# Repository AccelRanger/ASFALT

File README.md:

# ASFALT
**Accel Systems Line Following Robot**

A high-resolution line follower or edge follower calibrated for both usecases (TRD < for edge following, normal for line following) built on an Arduino Nano (ATmega328P), featuring a 16-sensor U-shaped IR array, custom KiCad PCBs, 3D-printed chassis parts, and a PID/proportional control algorithm with priority-based corner handling.

## License

This project is open source. Hardware designs, firmware, and mechanical files are provided as-is for personal and educational use.

---

*ASFALT — Accel Systems Line Following Robot*
*ASFALT-REV2 > Updated version single PCB, This repo has support till 1/10/2026

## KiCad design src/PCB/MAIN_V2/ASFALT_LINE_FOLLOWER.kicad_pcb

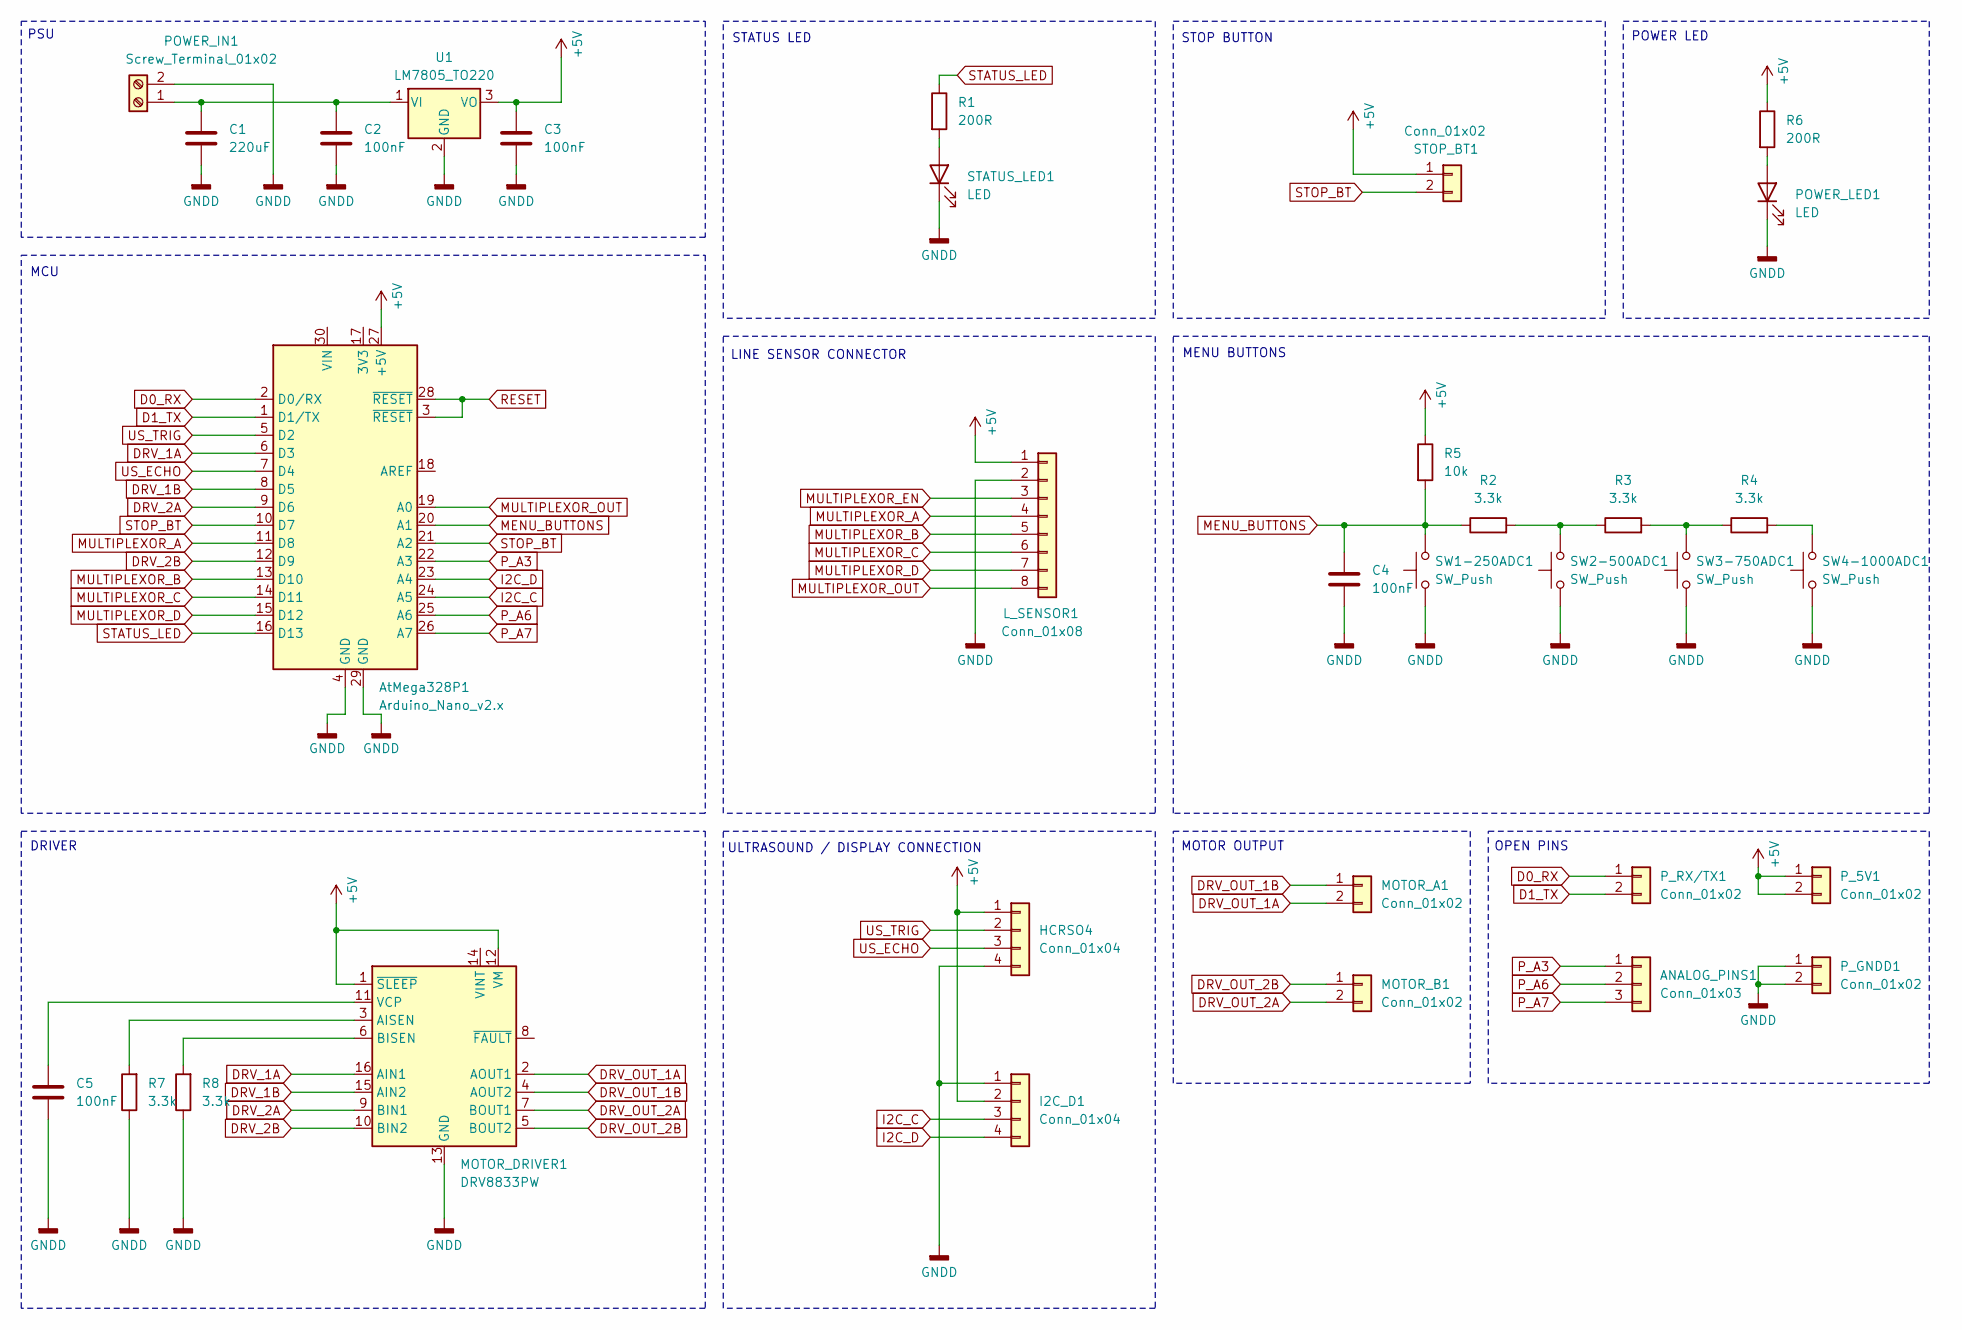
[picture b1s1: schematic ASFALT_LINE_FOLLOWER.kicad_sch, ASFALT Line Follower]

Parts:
ANALOG_PINS1: Conn_01x03; PinHeader_1x03_P2.54mm_Vertical
AtMega328P1: Arduino_Nano_v2.x; Arduino_Nano
C1: 220uF; C_0805_2012Metric_Pad1.18x1.45mm_HandSolder
C2, C3, C4, C5: 100nF; C_0805_2012Metric_Pad1.18x1.45mm_HandSolder
HCRSO4: Conn_01x04; PinHeader_1x04_P2.54mm_Vertical
I2C_D1: Conn_01x04; PinHeader_1x04_P2.54mm_Vertical
L_SENSOR1: Conn_01x08; PinHeader_1x08_P2.54mm_Vertical
MOTOR_A1: Conn_01x02; PinHeader_1x02_P2.54mm_Vertical
MOTOR_B1: Conn_01x02; PinHeader_1x02_P2.54mm_Vertical
MOTOR_DRIVER1: DRV8833PW; TSSOP-16_4.4x5mm_P0.65mm
POWER_IN1: Screw_Terminal_01x02; TerminalBlock_MaiXu_MX126-5.0-02P_1x02_P5.00mm
POWER_LED1: LED; LED_0805_2012Metric_Pad1.15x1.40mm_HandSolder
P_5V1: Conn_01x02; PinHeader_1x02_P2.54mm_Vertical
P_GNDD1: Conn_01x02; PinHeader_1x02_P2.54mm_Vertical
P_RX/TX1: Conn_01x02; PinHeader_1x02_P2.54mm_Vertical
R1, R6: 200R; R_0805_2012Metric_Pad1.20x1.40mm_HandSolder
R2, R3, R4, R7, R8: 3.3k; R_0805_2012Metric_Pad1.20x1.40mm_HandSolder
R5: 10k; R_0805_2012Metric_Pad1.20x1.40mm_HandSolder
STATUS_LED1: LED; LED_0805_2012Metric_Pad1.15x1.40mm_HandSolder
STOP_BT1: Conn_01x02; PinHeader_1x02_P2.54mm_Vertical
SW1-250ADC1, SW2-500ADC1, SW3-750ADC1, SW4-1000ADC1: SW_Push; SW_Push_1P1T_NO_CK_KSC6xxJ
U1: LM7805_TO220; TO-220-3_Vertical

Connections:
+5V: AtMega328P1.27 (+5V), C3.1, HCRSO4.1, I2C_D1.2, L_SENSOR1.1, MOTOR_DRIVER1.1 (~SLEEP), MOTOR_DRIVER1.12 (VM), P_5V1.1, P_5V1.2, R5.1, R6.1, STOP_BT1.1, U1.3 (VO)
D0_RX: AtMega328P1.2 (D0/RX), P_RX/TX1.1
D1_TX: AtMega328P1.1 (D1/TX), P_RX/TX1.2
DRV_1A: AtMega328P1.6 (D3), MOTOR_DRIVER1.16 (AIN1)
DRV_1B: AtMega328P1.8 (D5), MOTOR_DRIVER1.15 (AIN2)
DRV_2A: AtMega328P1.9 (D6), MOTOR_DRIVER1.9 (BIN1)
DRV_2B: AtMega328P1.12 (D9), MOTOR_DRIVER1.10 (BIN2)
DRV_OUT_1A: MOTOR_A1.2, MOTOR_DRIVER1.2 (AOUT1)
DRV_OUT_1B: MOTOR_A1.1, MOTOR_DRIVER1.4 (AOUT2)
DRV_OUT_2A: MOTOR_B1.2, MOTOR_DRIVER1.7 (BOUT1)
DRV_OUT_2B: MOTOR_B1.1, MOTOR_DRIVER1.5 (BOUT2)
GNDD: AtMega328P1.4 (GND), AtMega328P1.29 (GND), C1.2, C2.2, C3.2, C4.2, C5.2, HCRSO4.4, I2C_D1.1, L_SENSOR1.2, MOTOR_DRIVER1.13 (GND), POWER_IN1.2, POWER_LED1.1 (K), P_GNDD1.1, P_GNDD1.2, R7.1, R8.1, STATUS_LED1.1 (K), SW1-250ADC1.1, SW2-500ADC1.1, SW3-750ADC1.1, SW4-1000ADC1.1, U1.2 (GND)
I2C_C: AtMega328P1.24 (A5), I2C_D1.3
I2C_D: AtMega328P1.23 (A4), I2C_D1.4
MENU_BUTTONS: AtMega328P1.20 (A1), C4.1, R2.1, R5.2, SW1-250ADC1.2
MULTIPLEXOR_A: AtMega328P1.11 (D8), L_SENSOR1.4
MULTIPLEXOR_B: AtMega328P1.13 (D10), L_SENSOR1.5
MULTIPLEXOR_C: AtMega328P1.14 (D11), L_SENSOR1.6
MULTIPLEXOR_D: AtMega328P1.15 (D12), L_SENSOR1.7
MULTIPLEXOR_EN: L_SENSOR1.3
MULTIPLEXOR_OUT: AtMega328P1.19 (A0), L_SENSOR1.8
unnamed: MOTOR_DRIVER1.3 (AISEN), R7.2
unnamed: MOTOR_DRIVER1.6 (BISEN), R8.2
unnamed: C5.1, MOTOR_DRIVER1.11 (VCP)
unnamed: C1.1, C2.1, POWER_IN1.1, U1.1 (VI)
unnamed: POWER_LED1.2 (A), R6.2
unnamed: R2.2, R3.1, SW2-500ADC1.2
unnamed: R3.2, R4.1, SW3-750ADC1.2
unnamed: R4.2, SW4-1000ADC1.2
unnamed: R1.2, STATUS_LED1.2 (A)
P_A3: ANALOG_PINS1.1, AtMega328P1.22 (A3)
P_A6: ANALOG_PINS1.2, AtMega328P1.25 (A6)
P_A7: ANALOG_PINS1.3, AtMega328P1.26 (A7)
RESET: AtMega328P1.3 (~RESET), AtMega328P1.28 (~RESET)
STATUS_LED: AtMega328P1.16 (D13), R1.1
STOP_BT: AtMega328P1.10 (D7), AtMega328P1.21 (A2), STOP_BT1.2
US_ECHO: AtMega328P1.7 (D4), HCRSO4.3
US_TRIG: AtMega328P1.5 (D2), HCRSO4.2

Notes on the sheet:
MCU
MENU BUTTONS
OPEN PINS
PSU
ULTRASOUND / DISPLAY CONNECTION
POWER LED
LINE SENSOR CONNECTOR
DRIVER
STATUS LED
STOP BUTTON
MOTOR OUTPUT

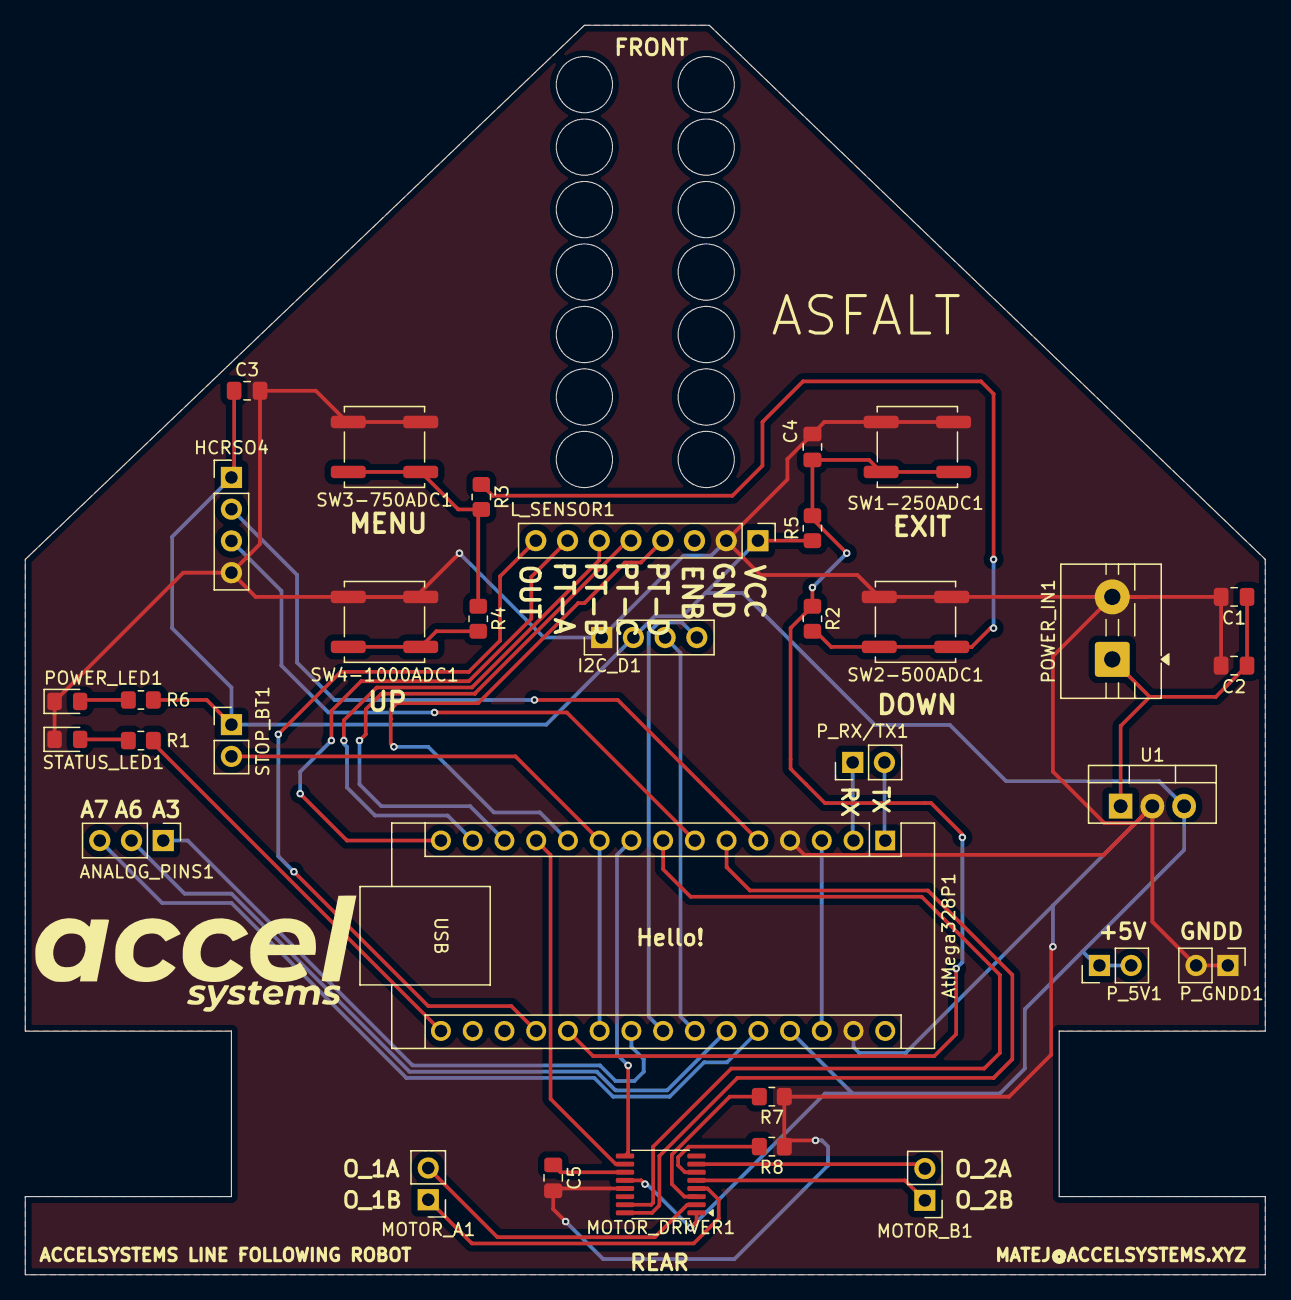
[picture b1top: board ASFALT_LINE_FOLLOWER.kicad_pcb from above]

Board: 2 copper layers, 99.2 x 100.0 mm, 33 parts (0 on the bottom side), 37 nets.

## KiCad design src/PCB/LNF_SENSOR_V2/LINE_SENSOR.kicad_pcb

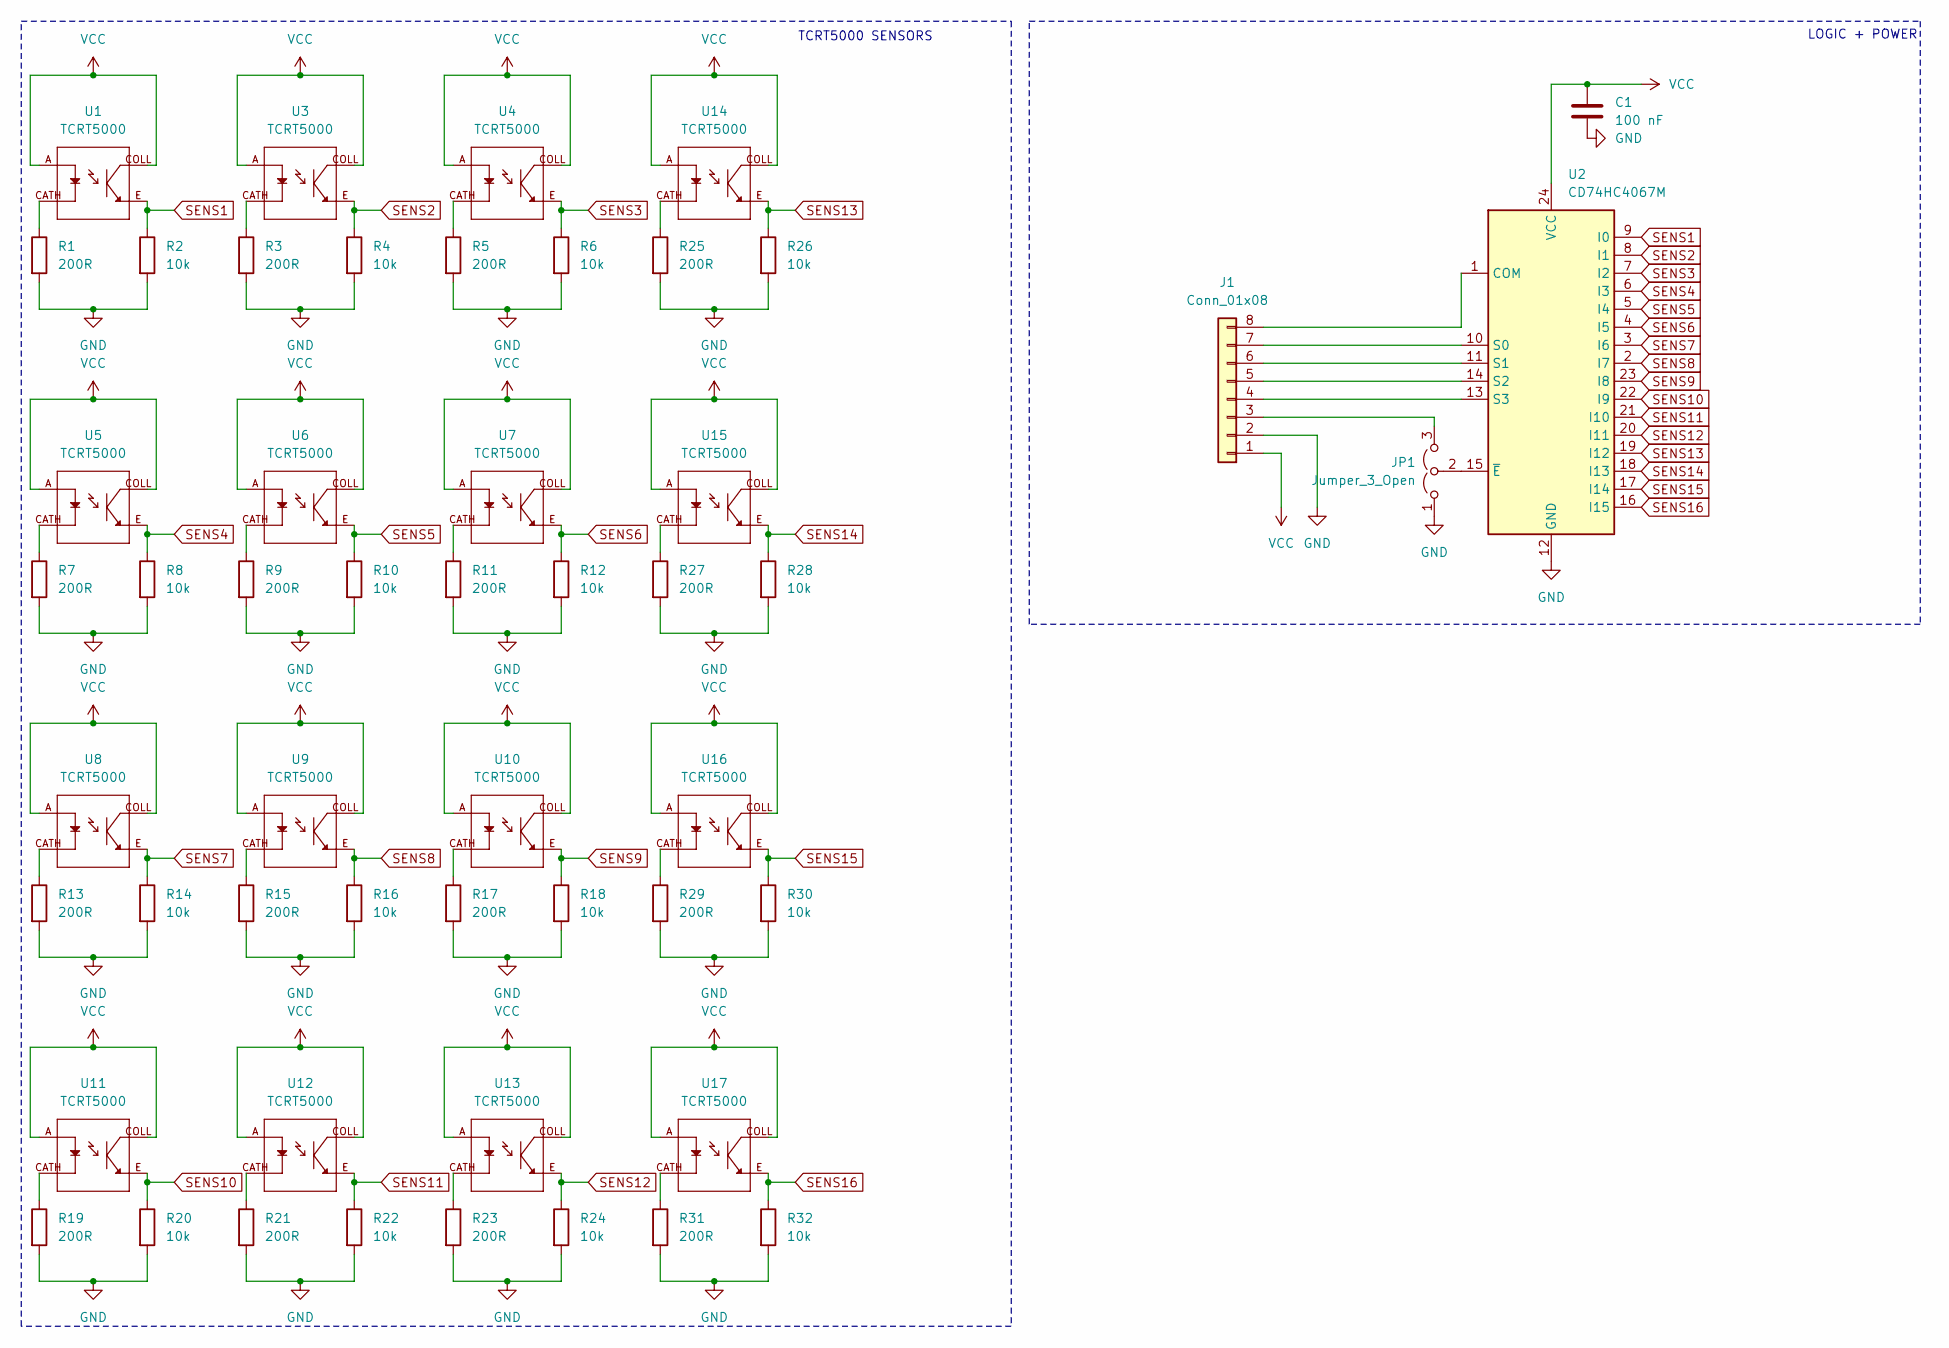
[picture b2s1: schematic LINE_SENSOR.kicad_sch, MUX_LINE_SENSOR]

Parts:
C1: 100 nF; C_0805_2012Metric
J1: Conn_01x08; PinHeader_1x08_P2.54mm_Vertical
JP1: Jumper_3_Open; SolderJumper-3_P1.3mm_Open_Pad1.0x1.5mm
R1, R3, R5, R7, R9, R11, R13, R15, R17, R19, R21, R23, R25, R27, R29, R31: 200R; R_0805_2012Metric
R2, R4, R6, R8, R10, R12, R14, R16, R18, R20, R22, R24, R26, R28, R30, R32: 10k; R_0805_2012Metric
U1, U3, U4, U5, U6, U7, U8, U9, U10, U11, U12, U13, U14, U15, U16, U17: TCRT5000; OPTO_TCRT5000; PARTREV 1.7
U2: CD74HC4067M; SOIC-24W_7.5x15.4mm_P1.27mm

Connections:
GND: C1.2, J1.2, JP1.1 (A), R1.2, R2.2, R3.2, R4.2, R5.2, R6.2, R7.2, R8.2, R9.2, R10.2, R11.2, R12.2, R13.2, R14.2, R15.2, R16.2, R17.2, R18.2, R19.2, R20.2, R21.2, R22.2, R23.2, R24.2, R25.2, R26.2, R27.2, R28.2, R29.2, R30.2, R31.2, R32.2, U2.12 (GND)
unnamed: J1.3, JP1.3 (B)
unnamed: J1.4, U2.13 (S3)
unnamed: J1.5, U2.14 (S2)
unnamed: J1.6, U2.11 (S1)
unnamed: J1.7, U2.10 (S0)
unnamed: J1.8, U2.1 (COM)
unnamed: JP1.2 (C), U2.15 (~E)
unnamed: R1.1, U1.CATH
unnamed: R3.1, U3.CATH
unnamed: R5.1, U4.CATH
unnamed: R7.1, U5.CATH
unnamed: R9.1, U6.CATH
unnamed: R11.1, U7.CATH
unnamed: R13.1, U8.CATH
unnamed: R15.1, U9.CATH
unnamed: R17.1, U10.CATH
unnamed: R19.1, U11.CATH
unnamed: R21.1, U12.CATH
unnamed: R23.1, U13.CATH
unnamed: R25.1, U14.CATH
unnamed: R27.1, U15.CATH
unnamed: R29.1, U16.CATH
unnamed: R31.1, U17.CATH
SENS1: R2.1, U1.E, U2.9 (I0)
SENS2: R4.1, U2.8 (I1), U3.E
SENS3: R6.1, U2.7 (I2), U4.E
SENS4: R8.1, U2.6 (I3), U5.E
SENS5: R10.1, U2.5 (I4), U6.E
SENS6: R12.1, U2.4 (I5), U7.E
SENS7: R14.1, U2.3 (I6), U8.E
SENS8: R16.1, U2.2 (I7), U9.E
SENS9: R18.1, U2.23 (I8), U10.E
SENS10: R20.1, U2.22 (I9), U11.E
SENS11: R22.1, U2.21 (I10), U12.E
SENS12: R24.1, U2.20 (I11), U13.E
SENS13: R26.1, U2.19 (I12), U14.E
SENS14: R28.1, U2.18 (I13), U15.E
SENS15: R30.1, U2.17 (I14), U16.E
SENS16: R32.1, U2.16 (I15), U17.E
VCC: C1.1, J1.1, U1.A, U1.COLL, U2.24 (VCC), U3.A, U3.COLL, U4.A, U4.COLL, U5.A, U5.COLL, U6.A, U6.COLL, U7.A, U7.COLL, U8.A, U8.COLL, U9.A, U9.COLL, U10.A, U10.COLL, U11.A, U11.COLL, U12.A, U12.COLL, U13.A, U13.COLL, U14.A, U14.COLL, U15.A, U15.COLL, U16.A, U16.COLL, U17.A, U17.COLL

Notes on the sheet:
TCRT5000 SENSORS
LOGIC + POWER

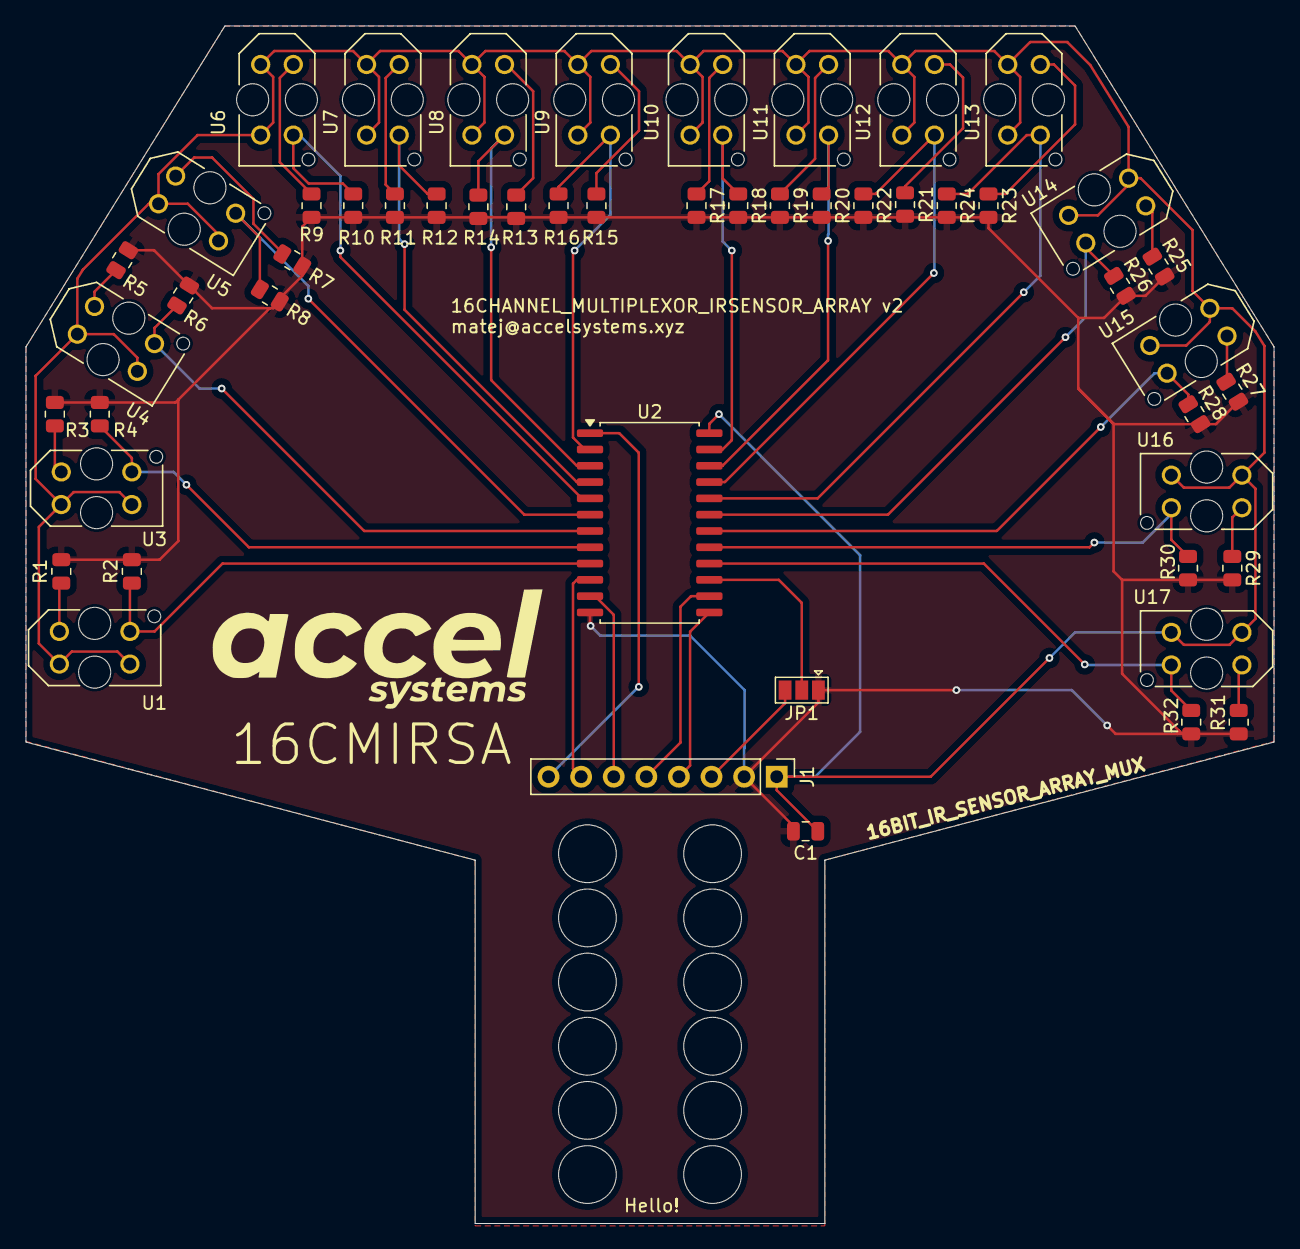
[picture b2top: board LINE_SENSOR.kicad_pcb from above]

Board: 2 copper layers, 97.2 x 93.3 mm, 52 parts (0 on the bottom side), 41 nets.

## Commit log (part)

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2026-02-14 Create a
2026-04-09 Create LNF_SENSOR_V1
2026-04-26 Rename src/3dPrint/motorMount/ASFALT_LINE_FOLLOWER_MOTOR_MOUNT.stl to src/3dPrint/motorMount/v1/ASFALT_LINE_FOLLOWER_MOTOR_MOUNT.stl
2026-04-26 Rename src/3dPrint/motorMount/ASFALT_LINE_FOLLOWER_MOTOR_MOUNT_V0.f3d to src/3dPrint/motorMount/v1/ASFALT_LINE_FOLLOWER_MOTOR_MOUNT_V0.f3d
2026-05-05 moved files
2026-05-05 Remove getting started, PCB, and 3D printing sections
    Removed getting started section, PCB details, and 3D printing information from README.
2026-05-05 repo organization
2026-05-07 new mutliplexor library
2026-05-13 archived files
2026-05-15 model insertion
2026-05-16 added a library for MuxSensor
2026-05-16 updated thruth tables and core files for library as for Header files and cpp files for MuxSensor library
2026-05-16 updated speeds
2026-05-18 update library and main code
2026-05-31 ACTUAL WORKING LINE FOLLOWER
2026-06-02 added integral clamp > PD >> PID
2026-06-02 Rename IMG_8839.jpg to robotFull.jpg
2026-06-02 Add robot image to README
    Added an image of the robot to the README.
2026-06-04 added new diag tool
2026-06-04 added docs for muxsensor
2026-06-04 added multiple checks for tof for obstacle avoidance and raised I2C speed
2026-06-04 fixed obstacle avoidance
    added timeouts for obstacle avoidance now just configuring
2026-06-04 fixed duped code in mux header lib
2026-06-05 added state machine for avoidance and added millis for avoidance and TOF
2026-06-06 updated regulators and avoidance and overall made it comptition ready
    t
2026-06-07 final version
2026-06-11 upDATE yay
